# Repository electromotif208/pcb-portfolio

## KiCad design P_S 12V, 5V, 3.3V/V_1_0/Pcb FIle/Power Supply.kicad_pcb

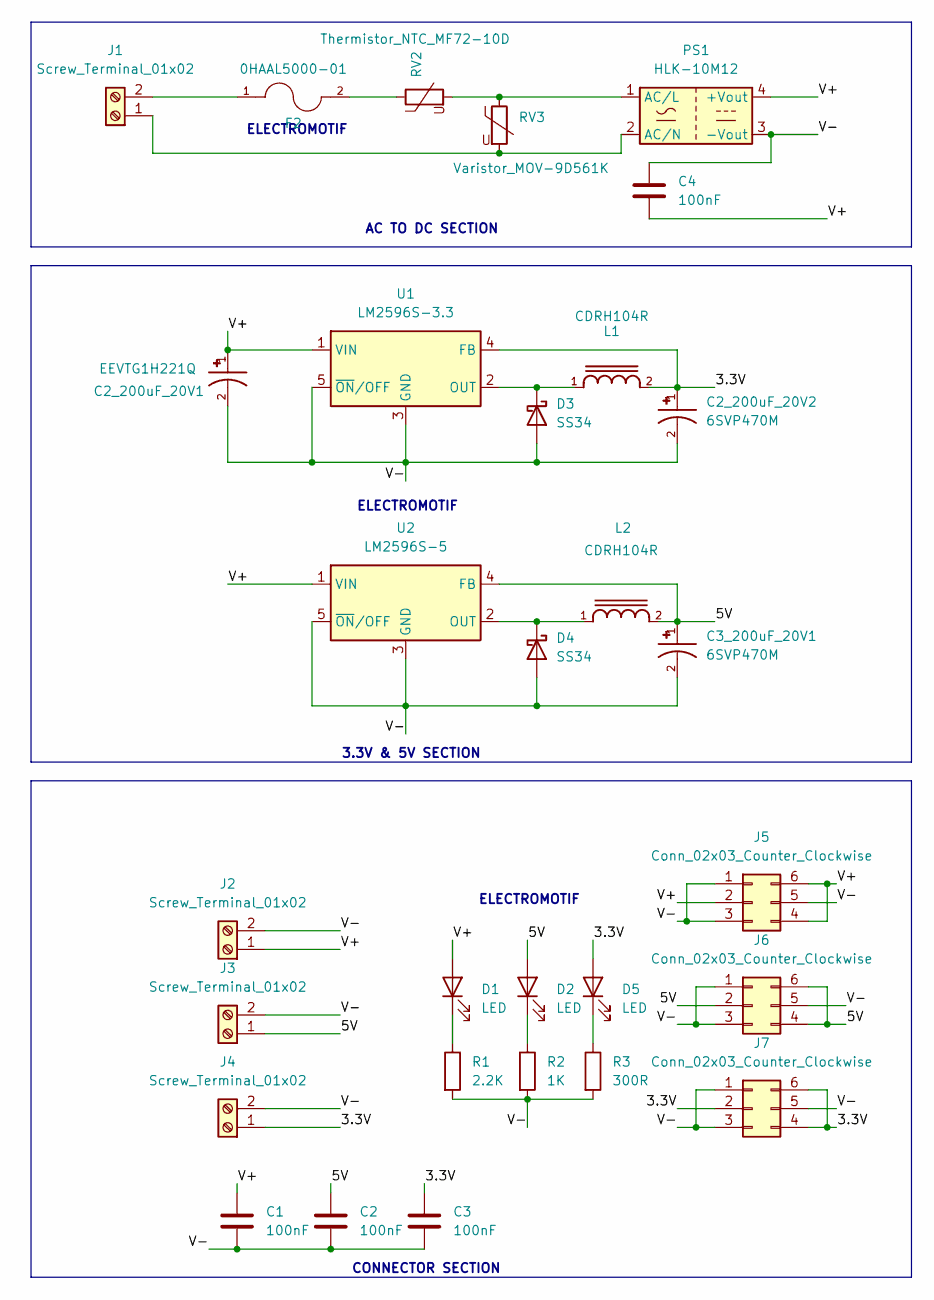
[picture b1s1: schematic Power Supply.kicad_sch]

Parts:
C1, C2, C3, C4: 100nF; C_0805_2012Metric_Pad1.18x1.45mm_HandSolder
C2_200uF_20V1: EEVTG1H221Q; CAP_EEVTG1H221Q; PARTREV 10-Oct-19
C2_200uF_20V2, C3_200uF_20V1: 6SVP470M; CAP_6SVP470M; PARTREV 28-Jun-19
D1, D2, D5: LED; LED_0805_2012Metric_Pad1.15x1.40mm_HandSolder
D3, D4: SS34; D_SMA
F2: 0HAAL5000-01; FUSRR508W60L840T400H810B; PARTREV Aug2024
J1, J2, J3, J4: Screw_Terminal_01x02; TerminalBlock_Xinya_XY308-2.54-2P_1x02_P2.54mm_Horizontal
J5, J6, J7: Conn_02x03_Counter_Clockwise; PinHeader_2x03_P2.54mm_Vertical
L1, L2: CDRH104R
PS1: HLK-10M12; Converter_ACDC_Hi-Link_HLK-10Mxx
R1: 2.2K; R_0805_2012Metric_Pad1.20x1.40mm_HandSolder
R2: 1K; R_0805_2012Metric_Pad1.20x1.40mm_HandSolder
R3: 300R; R_0805_2012Metric_Pad1.20x1.40mm_HandSolder
RV2: Thermistor_NTC_MF72-10D; C_Disc_D7.0mm_W2.5mm_P5.00mm
RV3: Varistor_MOV-9D561K; C_Disc_D7.0mm_W2.5mm_P5.00mm
U1: LM2596S-3.3; TO-263-5_TabPin3
U2: LM2596S-5; TO-263-5_TabPin3

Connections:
/3.3V: C2_200uF_20V2.1, C3.1, D5.2 (A), J4.1, J7.2, J7.4, J7.6, L1.2, U1.4 (FB)
/5V: C2.1, C3_200uF_20V1.1, D2.2 (A), J3.1, J6.2, J6.4, J6.6, L2.2, U2.4 (FB)
/V+: C1.1, C2_200uF_20V1.1, C4.2, D1.2 (A), J2.1, J5.2, J5.4, J5.6, PS1.4 (+Vout), U1.1 (VIN), U2.1 (VIN)
/V-: C1.2, C2.2, C2_200uF_20V1.2, C2_200uF_20V2.2, C3.2, C3_200uF_20V1.2, C4.1, D3.2 (A), D4.2 (A), J2.2, J3.2, J4.2, J5.1, J5.3, J5.5, J6.1, J6.3, J6.5, J7.1, J7.3, J7.5, PS1.3 (-Vout), R1.2, R2.2, R3.2, U1.3 (GND), U1.5 (~ON/OFF), U2.3 (GND), U2.5 (~ON/OFF)
unnamed: D1.1 (K), R1.1
unnamed: D2.1 (K), R2.1
unnamed: D3.1 (K), L1.1, U1.2 (OUT)
unnamed: D4.1 (K), L2.1, U2.2 (OUT)
unnamed: D5.1 (K), R3.1
unnamed: F2.2, RV2.1
unnamed: J1.1, PS1.2 (AC/N), RV3.2
unnamed: F2.1, J1.2
unnamed: PS1.1 (AC/L), RV2.2, RV3.1

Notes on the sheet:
ELECTROMOTIF
AC TO DC SECTION
3.3V & 5V SECTION
CONNECTOR SECTION

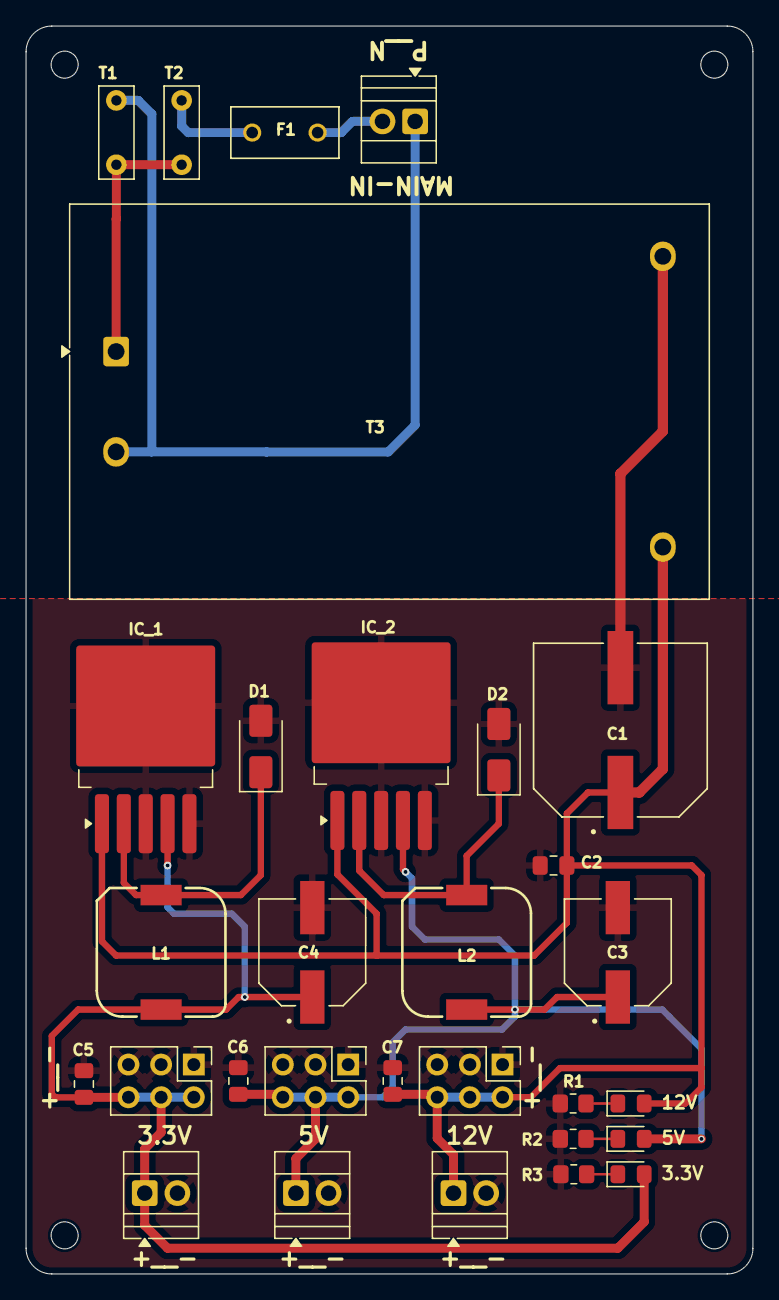
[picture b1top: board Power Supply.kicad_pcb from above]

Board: 2 copper layers, 56.5 x 97.0 mm, 30 parts (0 on the bottom side), 13 nets.
